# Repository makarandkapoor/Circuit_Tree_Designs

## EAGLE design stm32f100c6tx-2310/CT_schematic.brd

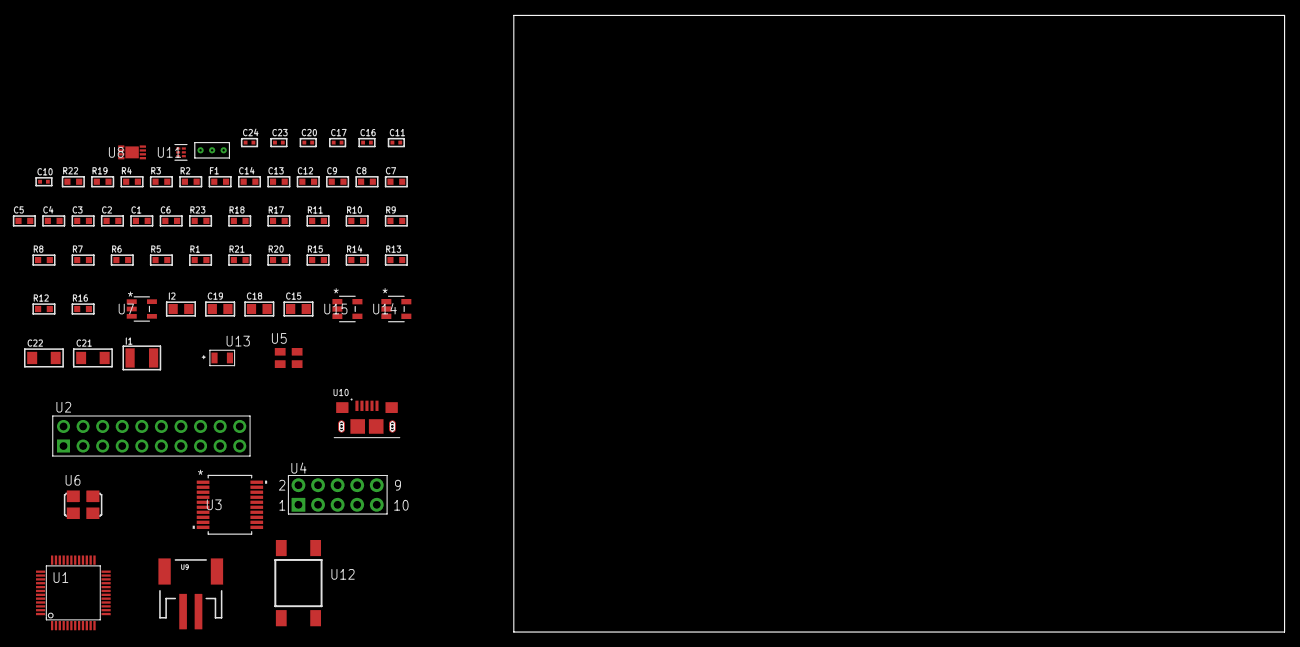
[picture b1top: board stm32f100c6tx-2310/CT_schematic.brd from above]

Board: 2 copper layers, 122.6 x 80.0 mm, 66 parts (0 on the bottom side), 45 nets, no tracks yet.

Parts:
C1, C9, C12, C13, C14: 1e-06; C0603
C2, C3, C4, C5: 1e-07; C0603
C6: 4.7e-06; C0603
C7, C8: 1e-08; C0603
C10, C11, C20: 1e-07; C0402
C15: 4.7e-06; C0805
C16, C17, C23, C24: 1e-08; C0402
C18, C19: 1e-05; C0805
C21, C22: 1e-05; C1206
F1: 240.0; L0603
I1: 1.5e-05; L1210
I2: 2.2e-06; L0805
R1, R5, R6, R7, R8, R9, R10, R11, R17, R18, R23: 10000.0; R0603
R2: 1000.0; R0603
R3: 1600.5; R0603
R4: 4700.0; R0603
R12, R13, R14: 100000.0; R0603
R15: 220000.0; R0603
R16: 1000000.0; R0603
R19: 9100.0; R0603
R20: 680000.0; R0603
R21: 120000.0; R0603
R22: 2000.0; R0603
U1: stm32f100c6t7; LQFP48
U2: TST-110-05-T-D-RA
U3: MAX3218EAP+T; SSOP-20
U4: HTSS-105-01-G-D
U5: ASEK-32.768KHz-ECST; ASEK
U6: ASFL1-25MHZ-NCS; ASFL1
U7: ltc3406es5; TSOT-23-5
U8: MCP73831T-2ACI/MC; DFN8_2X3MC
U9: S2B-PH-SM4-TB(LF)(SN); JST-2-SMD
U10: 10118193-0001LF; FCI_10118193-0001LF
U11: TPS3895ADRYR; SON-6
U12: 4-1437565-2; SW_4-1437565-2
U13: Q65110A2395; LGM67K-G1J2-24-Z
U14, U15: nc7sz125m5x; NC7SZ125M5X
U16: Dummy; DUMMY_PACKAGE_139

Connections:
CLK_U1_3: U1.3, U5.3
CLK_U1_5: U1.5, U6.3
GND: C1.2, C2.2, C3.2, C4.2, C5.2, C6.2, C7.2, C8.2, C9.2, C10.2, C11.2, C12.2, C13.2, C14.2, C16.2, C17.2, C18.2, C19.1, C19.2, C20.2, C21.2, C22.2, C23.2, C24.2, R2.2, R5.2, R11.2, R15.2, R19.2, R21.2, R22.2, U1.8, U1.23, U1.35, U1.47, U2.4, U2.6, U2.8, U2.10, U2.12, U2.14, U2.16, U2.18, U2.20, U3.5, U3.17, U3.20, U4.9, U5.2, U6.2, U7.2, U8.6, U8.9, U9.2, U10.5, U10.6, U10.7, U10.8, U10.9, U11.2, U13.C, U14.2, U14.3, U15.1, U15.3, U16.1
INPUT_USBPOWER_5V: C21.1, R23.2, U8.1, U8.2, U10.1
NET_U1_7: R4.1, U1.7, U15.4
NET_U1_9: C7.1, C8.1, C9.1, F1.1, U1.9
NET_U1_44: R5.1, U1.44
NET_U1_45: R3.1, U1.45, U13.A
NET_U1_46: R1.1, U1.46, U12.3, U12.4
NET_U2_3: R6.1, U2.3
NET_U2_7: R8.1, U2.7
NET_U2_9: R9.1, U2.9
NET_U2_19: R11.1, U2.19
NET_U3_1: I1.1, U3.1
NET_U3_2: R12.1, U3.2
NET_U3_3: R13.1, U3.3
NET_U3_4: R14.1, U3.4
NET_U3_15: C14.1, U3.15
NET_U3_16: C15.2, U3.16
NET_U3_18: C15.1, U3.18
NET_U3_19: C13.1, U3.19
NET_U4_3: U3.12, U4.3
NET_U4_4: U3.11, U4.4
NET_U4_5: U3.14, U4.5
NET_U4_6: U3.13, U4.6
NET_U7_3: I2.1, U7.3
NET_U7_5: R15.1, R16.1, U7.5
NET_U7_ATNET_3: I2.2, R16.2
NET_U8_5: R23.1, U8.5
NET_U8_8: R22.1, U8.8
NET_U11_1: R18.1, R19.1, U11.1
NET_U11_3: R20.2, R21.1, U11.3
NET_U11_4: R17.1, U11.4, U14.4, U15.2
NET_U12_1: R2.1, U12.1, U12.2
PROC_SYS_JTDI: R7.1, U1.38, U2.5
PROC_SYS_JTDO_TRACESWO: U1.39, U2.13
PROC_TIM1_CH1N: U1.17, U16.3
PROC_TIM1_CH3N: U1.19, U16.2
PROC_USART1_CTS: U1.32, U3.8
PROC_USART1_RTS: U1.33, U3.10
PROC_USART1_RX: U1.31, U3.9
PROC_USART1_TX: U1.30, U3.7
RST_OUT_U2_SRESET_B: R10.1, U2.15, U14.1
VCC_S1_3V7: C18.1, C22.1, U7.4, U8.3, U8.4, U9.1
VCC_TIER1_3V3: C1.1, C2.1, C3.1, C4.1, C5.1, C6.1, C10.1, C11.1, C12.1, C16.1, C17.1, C19.2, C20.1, C23.1, C24.1, F1.2, I1.2, I2.2, R1.2, R3.2, R4.2, R6.2, R7.2, R8.2, R9.2, R10.2, R12.2, R13.2, R14.2, R16.2, R17.2, R18.2, R20.1, U1.1, U1.24, U1.36, U1.48, U2.1, U2.2, U3.6, U5.4, U6.4, U11.6, U14.5, U15.5

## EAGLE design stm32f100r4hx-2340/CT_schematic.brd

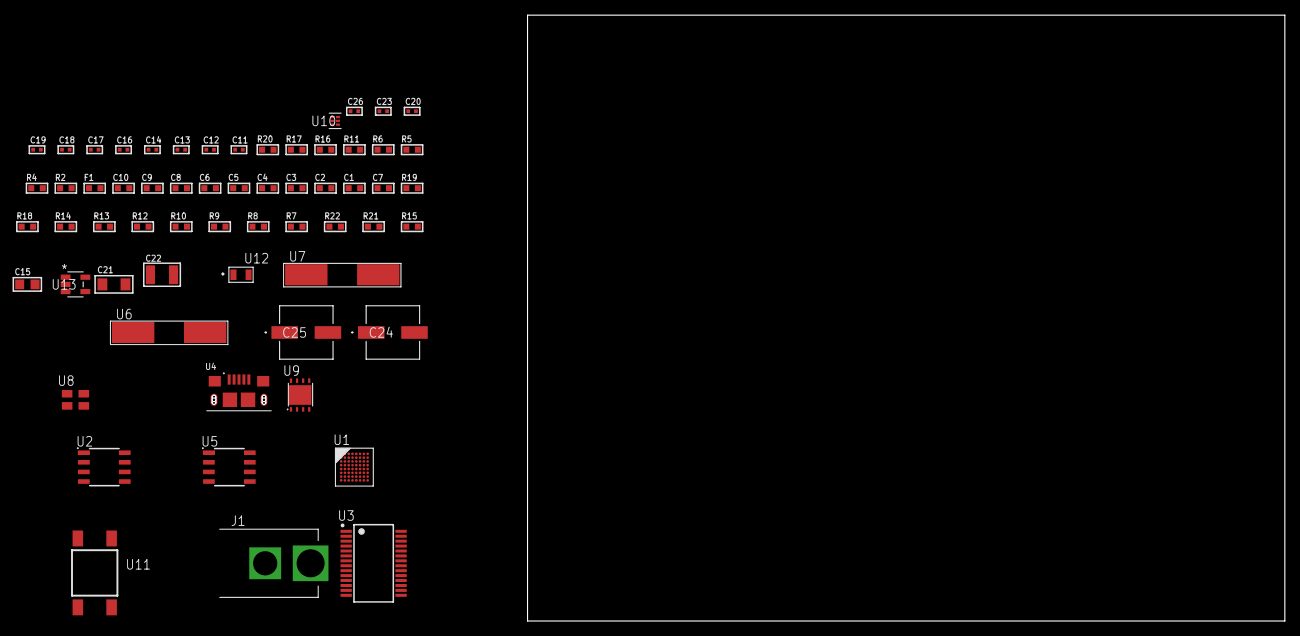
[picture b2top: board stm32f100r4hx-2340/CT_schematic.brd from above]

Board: 2 copper layers, 61 parts (0 on the bottom side), 34 nets, no tracks yet.

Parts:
C1, C10: 1e-06; C0603
C2, C3, C4, C5, C6: 1e-07; C0603
C7: 4.7e-06; C0603
C8, C9: 1e-08; C0603
C11, C12: 1e-11; C0402
C13, C18, C19, C20, C26: 1e-08; C0402
C14, C16, C17, C23: 1e-07; C0402
C15: 4.7e-06; C0805
C21: 1e-05; C1206
C22: 1e-05; C1210
C24, C25: 0.0001; EXV-9H
F1: 240.0; L0603
J1: PJ-037B; PJ-037B_PACKAGE
R2, R17: 1000.0; R0603
R4, R11: 4700.0; R0603
R5, R6: 2200.0; R0603
R7, R8, R9, R10, R12, R13, R14, R18, R19: 10000.0; R0603
R15: 100000.0; R0603
R16: 2231.0; R0603
R20: 9100.0; R0603
R21: 680000.0; R0603
R22: 120000.0; R0603
U1: stm32f100r4h7; TFBGA64
U2: AT25040B-SSHL-T; SOIC-8
U3: FT232RL-REEL; SSOP-28
U4: 10118193-0001LF; FCI_10118193-0001LF
U5: M24M02-DRMN6TP; SOIC-8
U6: ABLS-25.000MHZ-B2F-T
U7: ABLS-12.000MHZ-B4-T
U8: ASEK-32.768KHz-ECST; ASEK
U9: LP3878SDX-ADJ/NOPB; WSON-8
U10: TPS3895ADRYR; SON-6
U11: 4-1437565-2; SW_4-1437565-2
U12: Q65110A2395; LGM67K-G1J2-24-Z
U13: nc7sz125m5x; NC7SZ125M5X

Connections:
CLK_CRYSTAL_U1_C1: C11.1, U1.C1, U6.1
CLK_CRYSTAL_U1_D1: C12.1, U1.D1, U6.2
CLK_CRYSTAL_U3_27: U3.27, U7.1
CLK_CRYSTAL_U3_28: U3.28, U7.2
CLK_U1_A1: U1.A1, U8.3
GND: C1.2, C2.2, C3.2, C4.2, C5.2, C6.2, C7.2, C8.2, C9.2, C10.2, C11.2, C12.2, C13.2, C14.2, C15.2, C16.2, C17.2, C18.2, C19.2, C20.2, C21.2, C22.2, C23.2, C24.2, C25.2, C26.2, J1.2, R2.2, R7.2, R13.2, R14.2, R17.2, R20.2, R22.2, U1.C2, U1.D4, U1.D5, U1.D6, U1.F1, U2.4, U3.7, U3.18, U3.21, U3.25, U3.26, U4.5, U4.6, U4.7, U4.8, U4.9, U5.4, U8.2, U9.3, U9.PAD, U10.2, U12.C, U13.1, U13.3
NET_U1_A3: R6.1, U1.A3, U5.5
NET_U1_B3: R5.1, U1.B3, U5.6
NET_U1_B4: R7.1, U1.B4
NET_U1_E1: R4.1, U1.E1, U13.4
NET_U1_H1: C8.1, C9.1, C10.1, F1.1, U1.G1, U1.H1
NET_U1_H8: U11.3, U11.4
NET_U2_3: R8.1, U2.3
NET_U2_7: R10.1, U2.7
NET_U3_14: R12.1, U3.14
NET_U3_17: C16.1, U3.17
NET_U3_19: R13.1, U3.19
NET_U4_1: R11.1, U4.1
NET_U4_2: U3.16, U4.2
NET_U4_3: U3.15, U4.3
NET_U5_3: R14.1, U5.3
NET_U9_1: C20.1, U9.1
NET_U9_6: R16.2, R17.1, U9.6
NET_U9_8: R15.1, U9.8
NET_U10_1: R19.1, R20.1, U10.1
NET_U10_3: R21.2, R22.1, U10.3
NET_U10_4: R18.1, U10.4, U13.2
NET_U11_1: R2.1, U11.1, U11.2
PROC_SPI1_MISO: U1.A4, U2.2
PROC_SPI1_MOSI: U1.C4, U2.5
PROC_SPI1_NSS: R9.1, U1.A6, U2.1
PROC_SPI1_SCK: U1.A5, U2.6
VCC_S1_5V9: C21.1, C24.1, C25.1, J1.1, R15.2, U9.4
VCC_TIER1_3V3: C1.1, C2.1, C3.1, C4.1, C5.1, C6.1, C7.1, C13.1, C14.1, C15.1, C17.1, C18.1, C19.1, C22.1, C23.1, C26.1, F1.2, R4.2, R5.2, R6.2, R8.2, R9.2, R10.2, R12.2, R16.1, R18.2, R19.2, R21.1, U1.B2, U1.D2, U1.E4, U1.E5, U1.E6, U2.8, U3.4, U3.20, U5.8, U8.4, U9.5, U10.6, U13.5

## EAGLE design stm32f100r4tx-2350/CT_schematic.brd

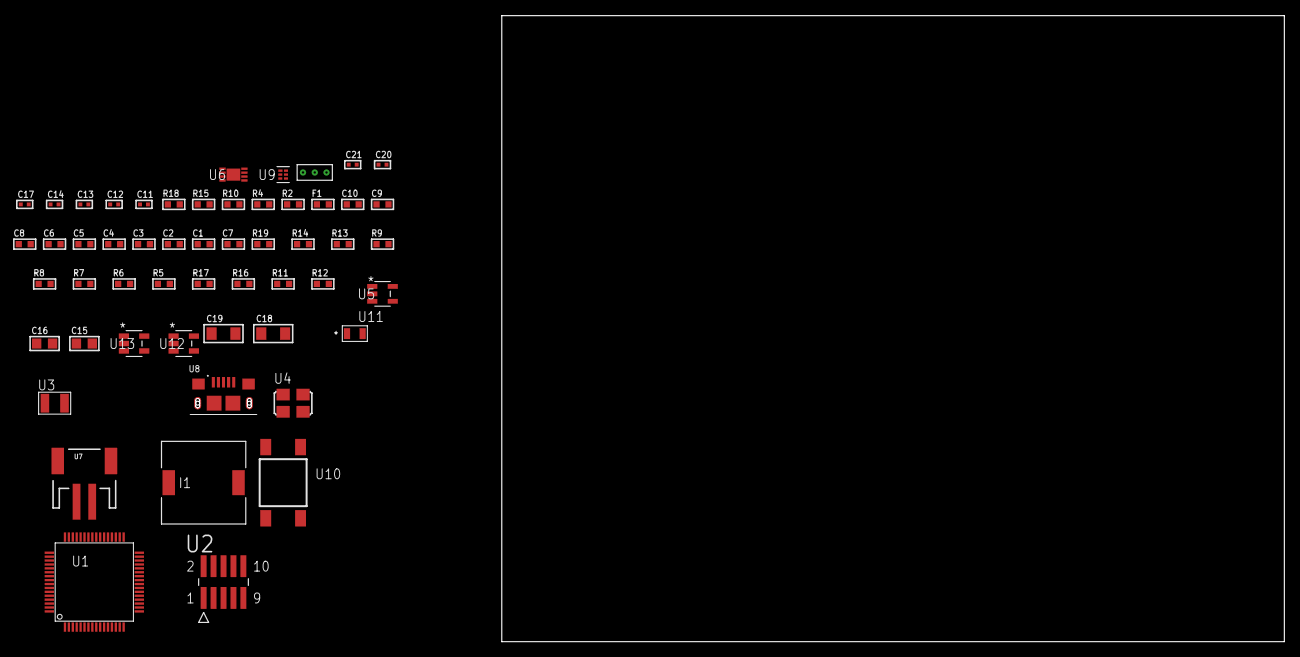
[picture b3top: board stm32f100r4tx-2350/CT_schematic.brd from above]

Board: 2 copper layers, 54 parts (0 on the bottom side), 28 nets, no tracks yet.

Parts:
C1, C10: 1e-06; C0603
C2, C3, C4, C5, C6: 1e-07; C0603
C7: 4.7e-06; C0603
C8, C9: 1e-08; C0603
C11, C12: 1e-11; C0402
C13, C17: 1e-07; C0402
C14, C20, C21: 1e-08; C0402
C15, C16: 1e-05; C0805
C18, C19: 1e-05; C1206
F1: 240.0; L0603
I1: 2.5e-06; DR1040
R2: 1000.0; R0603
R4: 4700.0; R0603
R5, R6, R7, R8, R9, R13, R14, R19: 10000.0; R0603
R10: 5.0; R0603
R11: 220000.0; R0603
R12: 1000000.0; R0603
R15: 9100.0; R0603
R16: 680000.0; R0603
R17: 120000.0; R0603
R18: 2000.0; R0603
U1: stm32f100r4t6; LQFP64
U2: FTSH-105-01-L-DV-K; SAMTEC_FTSH-105-01-L-DV-K
U3: ABS07-32.768KHZ-7-T
U4: ASFL1-25MHZ-NCS; ASFL1
U5: ltc3406es5; TSOT-23-5
U6: MCP73831T-2ACI/MC; DFN8_2X3MC
U7: S2B-PH-SM4-TB(LF)(SN); JST-2-SMD
U8: 10118193-0001LF; FCI_10118193-0001LF
U9: TPS3895ADRYR; SON-6
U10: 4-1437565-2; SW_4-1437565-2
U11: Q65110A2395; LGM67K-G1J2-24-Z
U12, U13: nc7sz125m5x; NC7SZ125M5X
U14: Dummy; DUMMY_PACKAGE_113

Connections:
CLK_CRYSTAL_U1_3: C11.1, U1.3, U3.1
CLK_CRYSTAL_U1_4: C12.1, U1.4, U3.2
CLK_U1_5: U1.5, U4.3
GND: C1.2, C2.2, C3.2, C4.2, C5.2, C6.2, C7.2, C8.2, C9.2, C10.2, C11.2, C12.2, C13.2, C14.2, C15.2, C16.1, C16.2, C17.2, C18.2, C19.2, C20.2, C21.2, R2.2, R5.2, R9.2, R10.2, R11.2, R15.2, R17.2, R18.2, U1.12, U1.18, U1.31, U1.47, U1.63, U2.3, U2.5, U4.2, U5.2, U6.6, U6.9, U7.2, U8.5, U8.6, U8.7, U8.8, U8.9, U9.2, U11.C, U12.2, U12.3, U13.1, U13.3, U14.1
INPUT_USBPOWER_5V: C18.1, R19.2, U6.1, U6.2, U8.1
NET_U1_7: R4.1, U1.7, U13.4
NET_U1_13: C8.1, C9.1, C10.1, F1.1, U1.13
NET_U1_60: R5.1, U1.60
NET_U1_62: U10.3, U10.4
NET_U2_2: R8.1, U2.2
NET_U2_4: R9.1, U2.4
NET_U2_9: R10.1, U2.9
NET_U5_3: I1.1, U5.3
NET_U5_5: R11.1, R12.1, U5.5
NET_U5_ATNET_3: I1.2, R12.2
NET_U6_5: R19.1, U6.5
NET_U6_8: R18.1, U6.8
NET_U9_1: R14.1, R15.1, U9.1
NET_U9_3: R16.2, R17.1, U9.3
NET_U9_4: R13.1, U9.4, U12.4, U13.2
NET_U10_1: R2.1, U10.1, U10.2
PROC_PC13_TAMPER_RTC: U1.2, U14.2
PROC_PD1_OSC_OUT: U1.6, U14.3
PROC_SYS_JTDI: R7.1, U1.50, U2.8
PROC_SYS_JTDO_TRACESWO: U1.55, U2.6
RST_OUT_U2_JTAG_RST_B: R6.1, U2.10, U12.1
VCC_S1_3V7: C15.1, C19.1, U5.4, U6.3, U6.4, U7.1
VCC_TIER1_3V3: C1.1, C2.1, C3.1, C4.1, C5.1, C6.1, C7.1, C13.1, C14.1, C16.2, C17.1, C20.1, C21.1, F1.2, I1.2, R4.2, R6.2, R7.2, R8.2, R12.2, R13.2, R14.2, R16.1, U1.1, U1.19, U1.32, U1.48, U1.64, U2.1, U4.4, U9.6, U12.5, U13.5

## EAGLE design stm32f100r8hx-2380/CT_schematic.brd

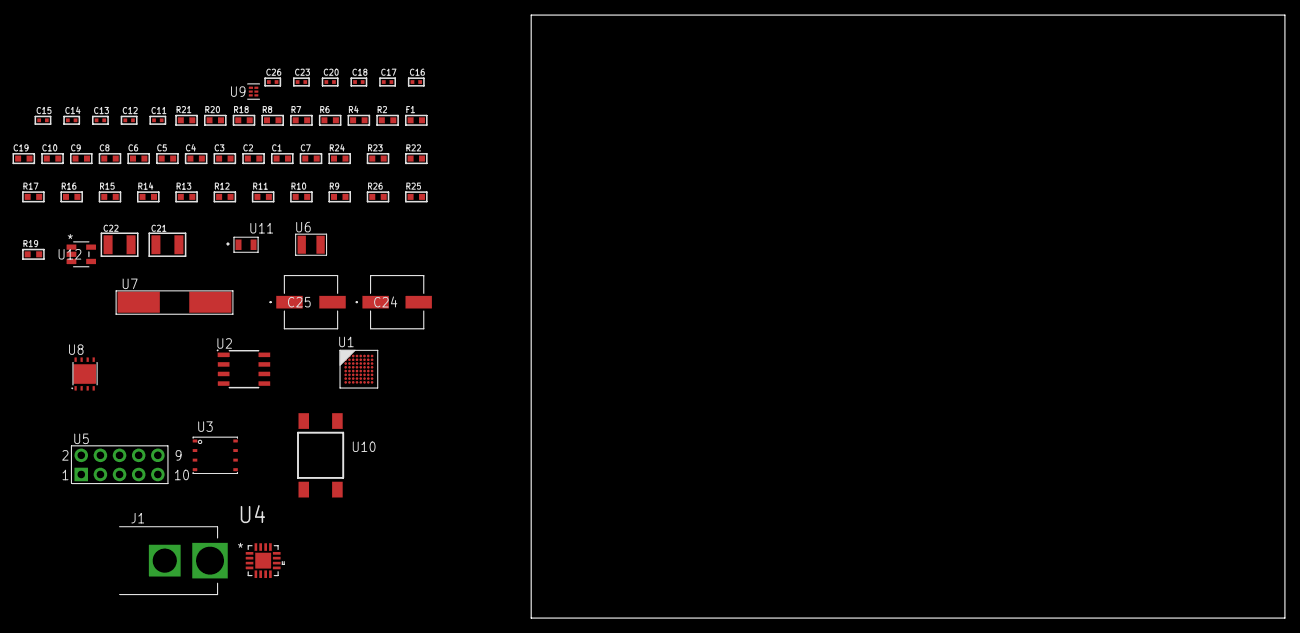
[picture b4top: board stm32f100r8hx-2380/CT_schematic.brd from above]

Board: 2 copper layers, 100.0 x 80.0 mm, 63 parts (0 on the bottom side), 38 nets, no tracks yet.

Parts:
C1, C10, C19: 1e-06; C0603
C2, C3, C4, C5, C6: 1e-07; C0603
C7: 4.7e-06; C0603
C8, C9: 1e-08; C0603
C11, C12, C13, C14: 1e-11; C0402
C15, C16, C20, C26: 1e-08; C0402
C17, C18, C23: 1e-07; C0402
C21, C22: 1e-05; C1210
C24, C25: 0.0001; EXV-9H
F1: 240.0; L0603
J1: PJ-037B; PJ-037B_PACKAGE
R2, R21: 1000.0; R0603
R4: 4700.0; R0603
R6, R7, R8: 2200.0; R0603
R9, R10, R11, R12, R13, R14, R15, R16, R17, R22, R23: 10000.0; R0603
R18: 47.0; R0603
R19: 100000.0; R0603
R20: 1500.0; R0603
R24: 18000.0; R0603
R25: 470000.0; R0603
R26: 120000.0; R0603
U1: stm32f100r8h6; TFBGA64
U2: AT25320B-SSHL-T; SOIC-8
U3: 24AA512-I/MF; DFN8-S
U4: TSC2013QRSARQ1; QFN65P400X400X100-17N
U5: HTSS-105-01-G-D
U6: ABS07-32.768KHZ-7-T
U7: ABLS-25.000MHZ-B2F-T
U8: LP3878SDX-ADJ/NOPB; WSON-8
U9: TPS3895ADRYR; SON-6
U10: 4-1437565-2; SW_4-1437565-2
U11: Q65110A2395; LGM67K-G1J2-24-Z
U12: nc7sz125m5x; NC7SZ125M5X

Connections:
CLK_CRYSTAL_U1_A1: C11.1, U1.A1, U6.1
CLK_CRYSTAL_U1_B1: C12.1, U1.B1, U6.2
CLK_CRYSTAL_U1_C1: C13.1, U1.C1, U7.1
CLK_CRYSTAL_U1_D1: C14.1, U1.D1, U7.2
GND: C1.2, C2.2, C3.2, C4.2, C5.2, C6.2, C7.2, C8.2, C9.2, C10.2, C11.2, C12.2, C13.2, C14.2, C15.2, C16.2, C20.2, C21.2, C22.2, C23.2, C24.2, C25.2, C26.2, J1.2, R2.2, R9.2, R13.2, R21.2, R24.2, R26.2, U1.C2, U1.D4, U1.D5, U1.D6, U1.F1, U2.4, U3.4, U4.17, U5.9, U8.3, U8.PAD, U9.2, U11.C, U12.1, U12.3
NET_U1_A3: R6.1, U1.A3, U4.1
NET_U1_B4: R9.1, U1.B4
NET_U1_E1: R4.1, U1.E1, U12.4
NET_U1_G7: R7.1, U1.G7, U3.6
NET_U1_H1: C8.1, C9.1, C10.1, F1.1, U1.G1, U1.H1
NET_U1_H7: R8.1, U1.H7, U3.5
NET_U1_H8: U10.3, U10.4
NET_U2_3: R10.1, U2.3
NET_U2_7: R12.1, U2.7
NET_U3_1: R13.1, U3.1
NET_U3_2: R14.1, U3.2
NET_U3_3: R15.1, U3.3
NET_U4_4: R17.1, U4.4
NET_U4_5: R16.1, U4.5
NET_U4_9: C17.2, C18.2, C19.2, R18.2, U4.9
NET_U4_15: R18.1, U4.8, U4.15
NET_U5_3: U4.12, U5.3
NET_U5_4: U4.14, U5.4
NET_U5_5: U4.11, U5.5
NET_U5_6: U4.13, U5.6
NET_U8_1: C20.1, U8.1
NET_U8_6: R20.2, R21.1, U8.6
NET_U8_8: R19.1, U8.8
NET_U9_1: R23.1, R24.1, U9.1
NET_U9_3: R25.2, R26.1, U9.3
NET_U9_4: R22.1, U9.4, U12.2
NET_U10_1: R2.1, U10.1, U10.2
PROC_SPI1_MISO: U1.A4, U2.2
PROC_SPI1_MOSI: U1.C4, U2.5
PROC_SPI1_NSS: R11.1, U1.A6, U2.1
PROC_SPI1_SCK: U1.A5, U2.6
VCC_S1_11V6: C21.1, C24.1, C25.1, J1.1, R19.2, U8.4
VCC_TIER1_2V5: C1.1, C2.1, C3.1, C4.1, C5.1, C6.1, C7.1, C15.1, C16.1, C17.1, C18.1, C19.1, C22.1, C23.1, C26.1, F1.2, R4.2, R6.2, R7.2, R8.2, R10.2, R11.2, R12.2, R14.2, R15.2, R16.2, R17.2, R20.1, R22.2, R23.2, R25.1, U1.B2, U1.D2, U1.E4, U1.E5, U1.E6, U2.8, U3.7, U3.8, U4.7, U4.10, U8.5, U9.6, U12.5

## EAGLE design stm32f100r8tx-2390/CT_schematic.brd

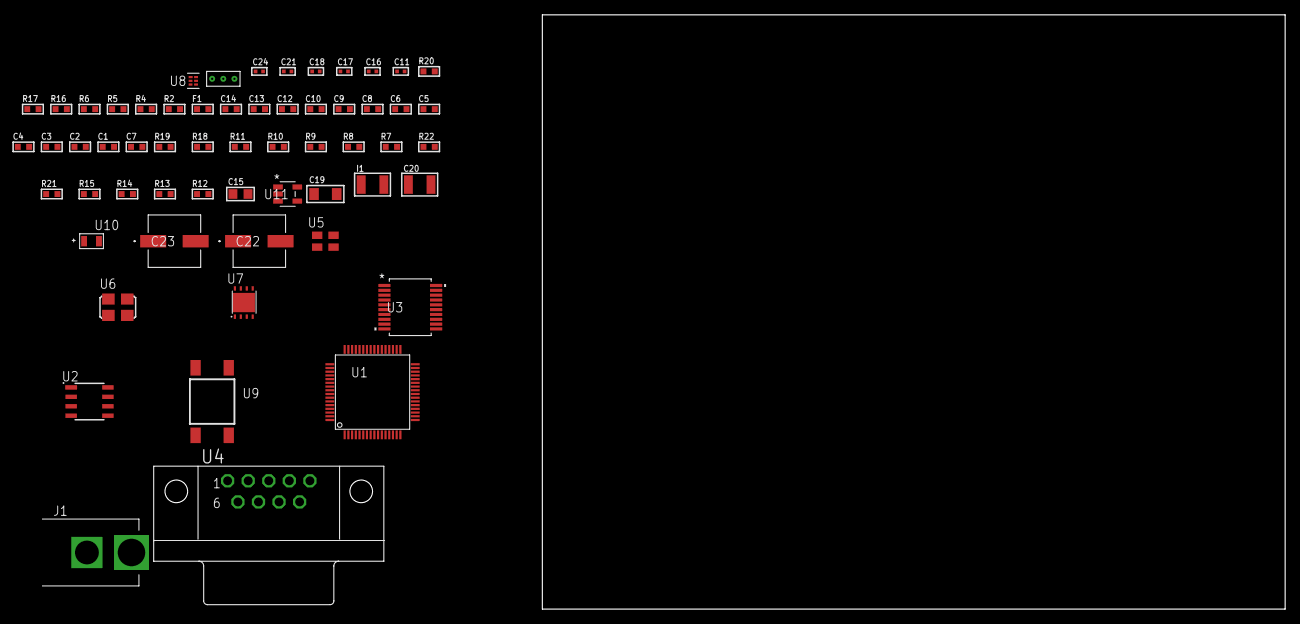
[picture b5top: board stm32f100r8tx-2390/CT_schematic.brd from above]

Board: 2 copper layers, 100.0 x 80.0 mm, 59 parts (0 on the bottom side), 40 nets, no tracks yet.

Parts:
C1, C10, C12, C13, C14: 1e-06; C0603
C2, C3, C4, C5, C6: 1e-07; C0603
C7: 4.7e-06; C0603
C8, C9: 1e-08; C0603
C11, C16, C17, C18, C24: 1e-08; C0402
C15: 4.7e-06; C0805
C19: 1e-05; C1206
C20: 1e-05; C1210
C21: 1e-07; C0402
C22, C23: 0.0001; EXV-9H
F1: 240.0; L0603
I1: 1.5e-05; L1210
J1: PJ-037B; PJ-037B_PACKAGE
R2, R17: 1000.0; R0603
R4: 4700.0; R0603
R5, R6: 2200.0; R0603
R7, R8, R9, R10, R11, R18, R19: 10000.0; R0603
R12, R13, R14, R15: 100000.0; R0603
R16: 2231.0; R0603
R20: 9100.0; R0603
R21: 680000.0; R0603
R22: 120000.0; R0603
U1: stm32f100r8t6; LQFP64
U2: AT24C02D-SSHM-T; AT24C02D
U3: MAX3218EAP+T; SSOP-20
U4: 182-009-113R531; 182-009-MALE
U5: ASEK-32.768KHz-ECST; ASEK
U6: ASFL1-25MHZ-NCS; ASFL1
U7: LP3878SDX-ADJ/NOPB; WSON-8
U8: TPS3895ADRYR; SON-6
U9: 4-1437565-2; SW_4-1437565-2
U10: Q65110A2395; LGM67K-G1J2-24-Z
U11: nc7sz125m5x; NC7SZ125M5X
U12: Dummy; DUMMY_PACKAGE_124

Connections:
CLK_U1_3: U1.3, U5.3
CLK_U1_5: U1.5, U6.3
GND: C1.2, C2.2, C3.2, C4.2, C5.2, C6.2, C7.2, C8.2, C9.2, C10.2, C11.2, C12.2, C13.2, C14.2, C16.2, C17.2, C18.2, C19.2, C20.2, C21.2, C22.2, C23.2, C24.2, J1.2, R2.2, R7.2, R8.2, R10.2, R11.2, R17.2, R20.2, R22.2, U1.12, U1.18, U1.31, U1.47, U1.63, U2.4, U3.5, U3.17, U3.20, U4.5, U5.2, U6.2, U7.3, U7.PAD, U8.2, U10.C, U11.1, U11.3, U12.1
NET_U1_7: R4.1, U1.7, U11.4
NET_U1_13: C8.1, C9.1, C10.1, F1.1, U1.13
NET_U1_58: R5.1, U1.58, U2.6
NET_U1_59: R6.1, U1.59, U2.5
NET_U1_60: R7.1, U1.60
NET_U1_62: U9.3, U9.4
NET_U2_1: R9.1, U2.1
NET_U2_2: R10.1, U2.2
NET_U2_3: R11.1, U2.3
NET_U2_7: R8.1, U2.7
NET_U3_1: I1.1, U3.1
NET_U3_2: R12.1, U3.2
NET_U3_3: R13.1, U3.3
NET_U3_4: R14.1, U3.4
NET_U3_15: C14.1, U3.15
NET_U3_16: C15.2, U3.16
NET_U3_18: C15.1, U3.18
NET_U3_19: C13.1, U3.19
NET_U4_2: U3.12, U4.2
NET_U4_3: U3.14, U4.3
NET_U4_7: U3.11, U4.7
NET_U4_8: U3.13, U4.8
NET_U7_1: C18.1, U7.1
NET_U7_6: R16.2, R17.1, U7.6
NET_U7_8: R15.1, U7.8
NET_U8_1: R19.1, R20.1, U8.1
NET_U8_3: R21.2, R22.1, U8.3
NET_U8_4: R18.1, U8.4, U11.2
NET_U9_1: R2.1, U9.1, U9.2
PROC_ADC1_IN3: U1.17, U12.3
PROC_ADC1_IN4: U1.20, U12.2
PROC_USART1_CTS: U1.44, U3.8
PROC_USART1_RTS: U1.45, U3.10
PROC_USART1_RX: U1.43, U3.9
PROC_USART1_TX: U1.42, U3.7
VCC_S1_10V1: C19.1, C22.1, C23.1, J1.1, R15.2, U7.4
VCC_TIER1_3V3: C1.1, C2.1, C3.1, C4.1, C5.1, C6.1, C7.1, C11.1, C12.1, C16.1, C17.1, C20.1, C21.1, C24.1, F1.2, I1.2, R4.2, R5.2, R6.2, R9.2, R12.2, R13.2, R14.2, R16.1, R18.2, R19.2, R21.1, U1.1, U1.19, U1.32, U1.48, U1.64, U2.8, U3.6, U5.4, U6.4, U7.5, U8.6, U11.5

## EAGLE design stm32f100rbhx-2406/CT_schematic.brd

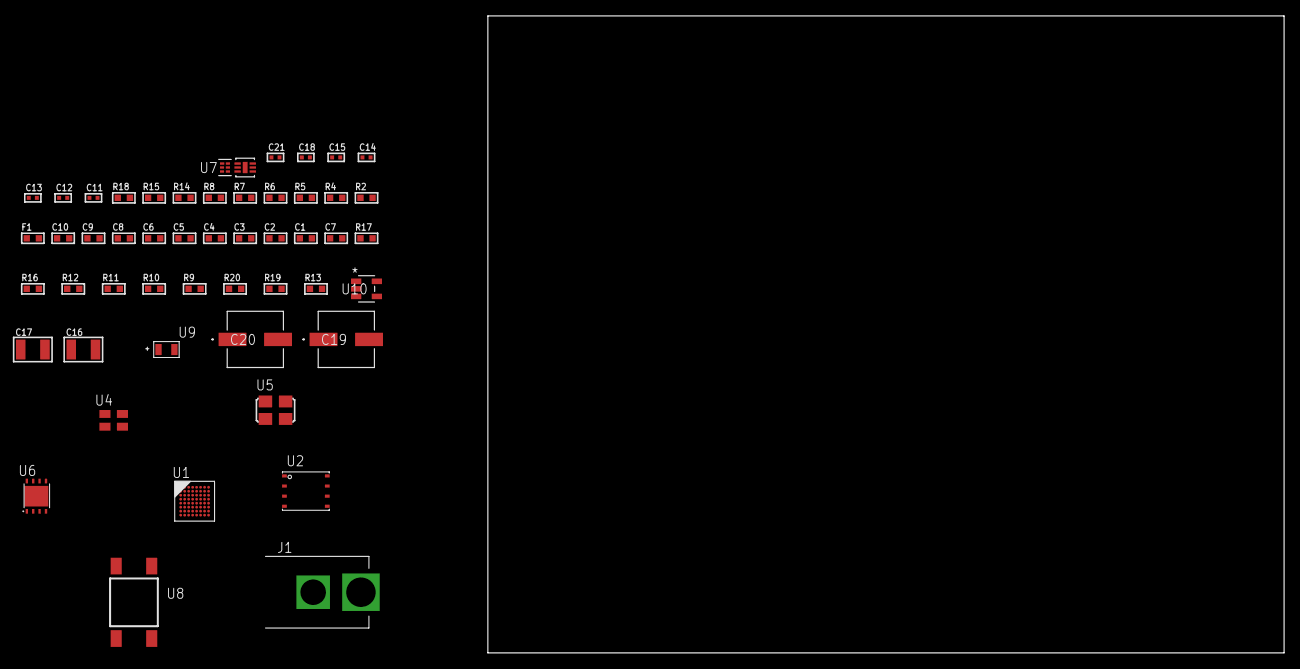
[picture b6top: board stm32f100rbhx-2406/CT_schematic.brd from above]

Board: 2 copper layers, 100.0 x 80.0 mm, 51 parts (0 on the bottom side), 23 nets, no tracks yet.

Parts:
C1, C10: 1e-06; C0603
C2, C3, C4, C5, C6: 1e-07; C0603
C7: 4.7e-06; C0603
C8, C9: 1e-08; C0603
C11, C13, C14, C15, C21: 1e-08; C0402
C12, C18: 1e-07; C0402
C16, C17: 1e-05; C1210
C19, C20: 0.0001; EXV-9H
F1: 240.0; L0603
J1: PJ-037B; PJ-037B_PACKAGE
R2, R15: 1000.0; R0603
R4: 4700.0; R0603
R5, R6, R7, R8: 2200.0; R0603
R9, R10, R11, R12, R16, R17: 10000.0; R0603
R13: 100000.0; R0603
R14: 2231.0; R0603
R18: 9100.0; R0603
R19: 680000.0; R0603
R20: 120000.0; R0603
U1: stm32f100rbh7; TFBGA64
U2: 24AA512-I/MF; DFN8-S
U3: SI7006-A20-IM; DFN-6
U4: ASEK-32.768KHz-ECST; ASEK
U5: ASFL1-25MHZ-NCS; ASFL1
U6: LP3878SDX-ADJ/NOPB; WSON-8
U7: TPS3895ADRYR; SON-6
U8: 4-1437565-2; SW_4-1437565-2
U9: Q65110A2395; LGM67K-G1J2-24-Z
U10: nc7sz125m5x; NC7SZ125M5X

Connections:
CLK_U1_A1: U1.A1, U4.3
CLK_U1_C1: U1.C1, U5.3
GND: C1.2, C2.2, C3.2, C4.2, C5.2, C6.2, C7.2, C8.2, C9.2, C10.2, C11.2, C12.2, C13.2, C14.2, C15.2, C16.2, C17.2, C18.2, C19.2, C20.2, C21.2, J1.2, R2.2, R9.2, R11.2, R12.2, R15.2, R18.2, R20.2, U1.C2, U1.D4, U1.D5, U1.D6, U1.F1, U2.4, U2.7, U3.2, U3.7, U4.2, U5.2, U6.3, U6.PAD, U7.2, U9.C, U10.1, U10.3
NET_U1_A3: R6.1, U1.A3, U3.1
NET_U1_B3: R5.1, U1.B3, U3.6
NET_U1_B4: R9.1, U1.B4
NET_U1_E1: R4.1, U1.E1, U10.4
NET_U1_G7: R7.1, U1.G7, U2.6
NET_U1_H1: C8.1, C9.1, C10.1, F1.1, U1.G1, U1.H1
NET_U1_H7: R8.1, U1.H7, U2.5
NET_U1_H8: U8.3, U8.4
NET_U2_1: R10.1, U2.1
NET_U2_2: R11.1, U2.2
NET_U2_3: R12.1, U2.3
NET_U6_1: C15.1, U6.1
NET_U6_6: R14.2, R15.1, U6.6
NET_U6_8: R13.1, U6.8
NET_U7_1: R17.1, R18.1, U7.1
NET_U7_3: R19.2, R20.1, U7.3
NET_U7_4: R16.1, U7.4, U10.2
NET_U8_1: R2.1, U8.1, U8.2
VCC_S1_15V8: C16.1, C19.1, C20.1, J1.1, R13.2, U6.4
VCC_TIER1_3V3: C1.1, C2.1, C3.1, C4.1, C5.1, C6.1, C7.1, C11.1, C12.1, C13.1, C14.1, C17.1, C18.1, C21.1, F1.2, R4.2, R5.2, R6.2, R7.2, R8.2, R10.2, R14.1, R16.2, R17.2, R19.1, U1.B2, U1.D2, U1.E4, U1.E5, U1.E6, U2.8, U3.5, U4.4, U5.4, U6.5, U7.6, U10.5

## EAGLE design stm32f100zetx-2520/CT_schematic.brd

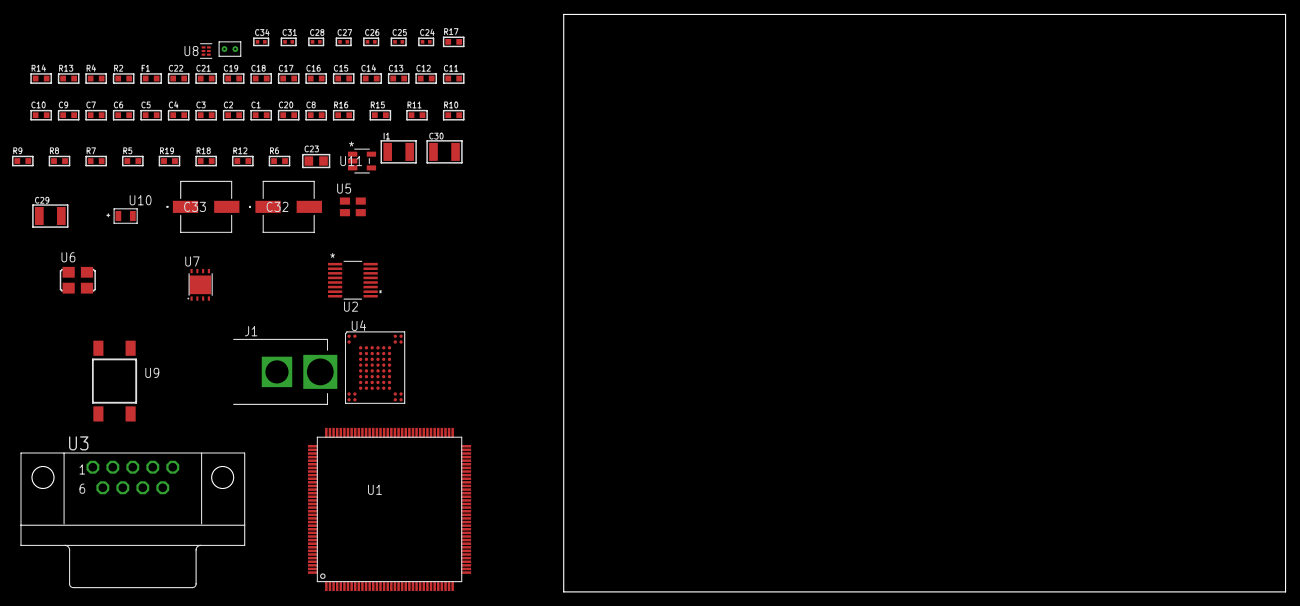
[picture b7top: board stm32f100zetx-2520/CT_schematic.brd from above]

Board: 2 copper layers, 100.0 x 80.0 mm, 66 parts (0 on the bottom side), 41 nets, no tracks yet.

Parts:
C1, C17, C18, C19, C21, C22: 1e-06; C0603
C2, C3, C4, C5, C6, C7, C9, C10, C11, C12, C13, C14: 1e-07; C0603
C8: 4.7e-06; C0603
C15, C16: 1e-08; C0603
C20: 2.2e-07; C0603
C23: 1e-05; C0805
C24, C25, C31: 1e-07; C0402
C26, C27, C28, C34: 1e-08; C0402
C29, C30: 1e-05; C1210
C32, C33: 0.0001; EXV-9H
F1: 240.0; L0603
I1: 1e-05; L1210
J1: PJ-037B; PJ-037B_PACKAGE
R2, R14: 1000.0; R0603
R4: 4700.0; R0603
R5, R7, R8, R9, R10, R11, R15, R16: 10000.0; R0603
R6, R12: 100000.0; R0603
R13: 2231.0; R0603
R17: 9100.0; R0603
R18: 680000.0; R0603
R19: 120000.0; R0603
U1: stm32f100zet6; LQFP144
U2: LTC2804CGN-1#PBF; SSOP-16
U3: 182-009-113R531; 182-009-MALE
U4: TH58NVG3S0HBAI4
U5: ASEK-32.768KHz-ECST; ASEK
U6: ASFL1-25MHZ-NCS; ASFL1
U7: LP3878SDX-ADJ/NOPB; WSON-8
U8: TPS3895ADRYR; SON-6
U9: 4-1437565-2; SW_4-1437565-2
U10: Q65110A2395; LGM67K-G1J2-24-Z
U11: nc7sz125m5x; NC7SZ125M5X
U12: Dummy; DUMMY_PACKAGE_140

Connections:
CLK_U1_8: U1.8, U5.3
CLK_U1_23: U1.23, U6.3
GND: C1.2, C2.2, C3.2, C4.2, C5.2, C6.2, C7.2, C8.2, C9.2, C10.2, C11.2, C12.2, C13.2, C14.2, C15.2, C16.2, C17.2, C18.2, C19.2, C21.2, C22.2, C23.2, C24.2, C25.2, C26.2, C27.2, C28.2, C29.2, C30.2, C31.2, C32.2, C33.2, C34.2, J1.2, R2.2, R5.2, R14.2, R17.2, R19.2, U1.16, U1.30, U1.31, U1.38, U1.51, U1.61, U1.71, U1.83, U1.94, U1.107, U1.120, U1.130, U1.143, U2.8, U3.5, U4.C5, U4.K3, U4.K8, U5.2, U6.2, U7.3, U7.PAD, U8.2, U10.C, U11.1, U11.3, U12.1
NET_U1_25: R4.1, U1.25, U11.4
NET_U1_33: C15.1, C16.1, C17.1, F1.1, U1.32, U1.33
NET_U1_138: R5.1, U1.138
NET_U1_142: U9.3, U9.4
NET_U2_6: C18.1, U2.6
NET_U2_7: C20.1, I1.2, U2.7
NET_U2_9: C19.1, U2.9
NET_U2_10: C20.2, U2.10
NET_U2_11: R6.1, U2.11
NET_U3_2: U2.1, U3.2
NET_U3_3: U2.3, U3.3
NET_U3_7: U2.2, U3.7
NET_U3_8: U2.4, U3.8
NET_U4_C3: R10.1, U4.C3
NET_U4_C6: R7.1, U4.C6
NET_U4_C8: R11.1, U4.C8
NET_U7_1: C28.1, U7.1
NET_U7_6: R13.2, R14.1, U7.6
NET_U7_8: R12.1, U7.8
NET_U8_1: R16.1, R17.1, U8.1
NET_U8_3: R18.2, R19.1, U8.3
NET_U8_4: R15.1, U8.4, U11.2
NET_U9_1: R2.1, U9.1, U9.2
PROC_DAC_OUT2: U1.41, U12.2
PROC_FSMC_D0: U1.85, U4.H4
PROC_FSMC_D1: U1.86, U4.J4
PROC_FSMC_D2: U1.114, U4.K4
PROC_FSMC_D3: U1.115, U4.K5
PROC_FSMC_D4: U1.58, U4.K6
PROC_FSMC_D5: U1.59, U4.J7
PROC_FSMC_D6: U1.60, U4.K7
PROC_FSMC_D7: U1.63, U4.J8
PROC_FSMC_NOE: R8.1, U1.118, U4.D4
PROC_FSMC_NWE: R9.1, U1.119, U4.C7
PROC_UART4_RX: U1.112, U2.16
PROC_UART4_TX: U1.111, U2.14
VCC_S1_12V7: C29.1, C32.1, C33.1, J1.1, R12.2, U7.4
VCC_TIER1_3V3: C1.1, C2.1, C3.1, C4.1, C5.1, C6.1, C7.1, C8.1, C9.1, C10.1, C11.1, C12.1, C13.1, C14.1, C21.1, C22.1, C23.1, C24.1, C25.1, C26.1, C27.1, C30.1, C31.1, C34.1, F1.2, I1.1, R4.2, R6.2, R7.2, R8.2, R9.2, R10.2, R11.2, R13.1, R15.2, R16.2, R18.1, U1.6, U1.17, U1.39, U1.52, U1.62, U1.72, U1.84, U1.95, U1.108, U1.121, U1.131, U1.144, U2.5, U2.12, U4.H8, U4.J6, U5.4, U6.4, U7.5, U8.6, U11.5

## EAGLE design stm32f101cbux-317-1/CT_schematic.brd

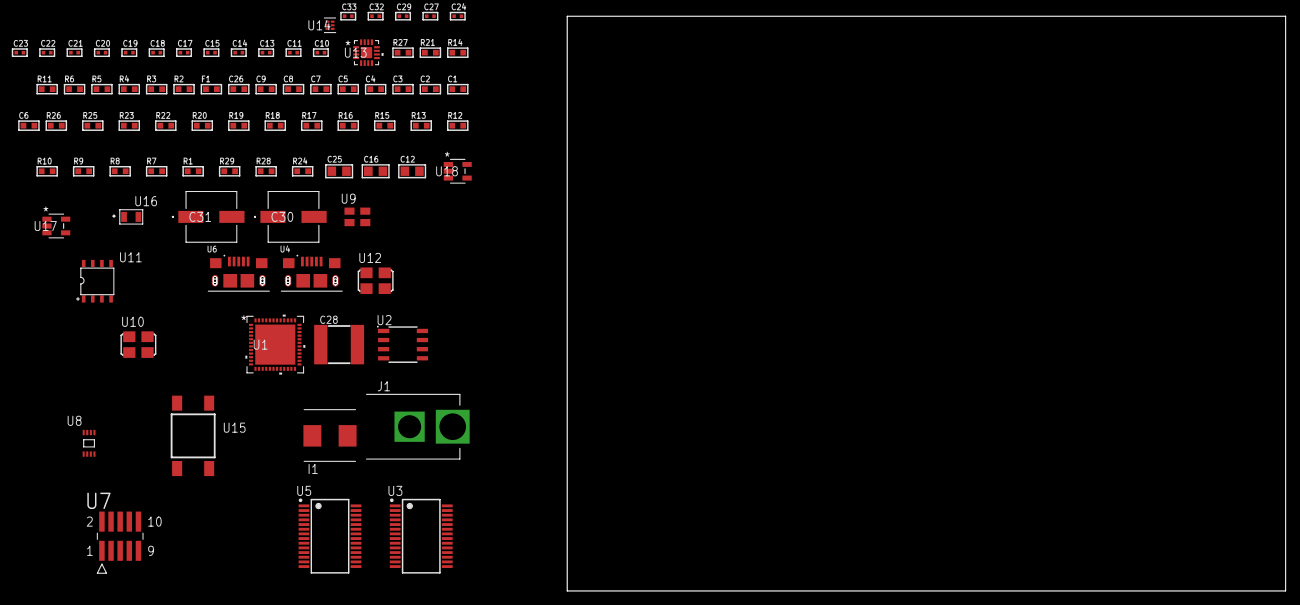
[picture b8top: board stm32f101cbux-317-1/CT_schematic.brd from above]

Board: 2 copper layers, 83 parts (0 on the bottom side), 56 nets, no tracks yet.

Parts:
C1, C9, C26: 1e-06; C0603
C2, C3, C4, C5: 1e-07; C0603
C6: 4.7e-06; C0603
C7, C8: 1e-08; C0603
C10, C20, C21, C22, C23, C24, C32, C33: 1e-08; C0402
C11, C13, C14, C15, C17, C18, C19, C27, C29: 1e-07; C0402
C12, C16: 4.7e-06; C0805
C25: 1e-05; C0805
C28: 6.8e-05; 2220
C30, C31: 0.0001; EXV-9H
F1: 240.0; L0603
I1: 3.3e-06; WE-HCI_7030/7040/7050
J1: PJ-037B; PJ-037B_PACKAGE
R1, R7, R8, R9, R10, R12, R13, R15, R16, R17, R18, R19, R20, R25, R26: 10000.0; R0603
R2: 1000.0; R0603
R3: 1600.5; R0603
R4, R11, R14: 4700.0; R0603
R5, R6: 2200.0; R0603
R21: 5.0; R0603
R22: 20000.0; R0603
R23: 91000.0; R0603
R24: 300000.0; R0603
R27: 9100.0; R0603
R28: 680000.0; R0603
R29: 120000.0; R0603
U1: STM32F101CBU6; UFQFPN48
U2: AT25512N-SH-T; SOIC-8
U3, U5: FT232RL-REEL; SSOP-28
U4, U6: 10118193-0001LF; FCI_10118193-0001LF
U7: FTSH-105-01-L-DV-K; SAMTEC_FTSH-105-01-L-DV-K
U8: 24AA02T-I/MNY; TDFN-8/6MM
U9: ASEK-32.768KHz-ECST; ASEK
U10: ASFL1-12MHZ-NCS; ASFL1
U11: idt74fct38072; IDT74FCT38072
U12: ASFL1-25MHZ-NCS; ASFL1
U13: LTC3601EUD#PBF; QFN-16_EP
U14: TPS3895ADRYR; SON-6
U15: 4-1437565-2; SW_4-1437565-2
U16: Q65110A2395; LGM67K-G1J2-24-Z
U17, U18: nc7sz125m5x; NC7SZ125M5X

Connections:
CLK_U1_3: U1.3, U9.3
CLK_U1_5: U1.5, U12.3
CLK_U3_27: U3.27, U11.7
CLK_U5_27: U5.27, U11.6
CLK_U11_3: U10.3, U11.3
GND: C1.2, C2.2, C3.2, C4.2, C5.2, C6.2, C7.2, C8.2, C9.2, C10.2, C11.2, C12.2, C13.2, C14.2, C15.2, C16.2, C17.2, C18.2, C19.2, C20.2, C21.2, C22.2, C23.2, C24.2, C25.2, C26.2, C28.1, C28.2, C29.2, C30.2, C31.2, C32.2, C33.2, J1.2, R2.2, R7.2, R13.2, R16.2, R20.2, R21.2, R22.2, R24.2, R27.2, R29.2, U1.8, U1.23, U1.35, U1.47, U1.49, U2.4, U3.7, U3.18, U3.21, U3.25, U3.26, U4.5, U4.6, U4.7, U4.8, U4.9, U5.7, U5.18, U5.21, U5.25, U5.26, U6.5, U6.6, U6.7, U6.8, U6.9, U7.3, U7.5, U8.4, U8.7, U9.2, U10.2, U11.4, U11.5, U11.8, U12.2, U13.1, U13.9, U13.17, U14.2, U16.C, U17.2, U17.3, U18.1, U18.3
NET_U1_7: R4.1, U1.7, U18.4
NET_U1_9: C7.1, C8.1, C9.1, F1.1, U1.9
NET_U1_42: R5.1, U1.42, U8.6
NET_U1_43: R6.1, U1.43, U8.5
NET_U1_44: R7.1, U1.44
NET_U1_45: R3.1, U1.45, U16.A
NET_U1_46: R1.1, U1.46, U15.3, U15.4
NET_U2_3: R8.1, U2.3
NET_U2_7: R10.1, U2.7
NET_U3_14: R12.1, U3.14
NET_U3_17: C13.1, U3.17
NET_U3_19: R13.1, U3.19
NET_U4_1: R11.1, U4.1
NET_U4_2: U3.16, U4.2
NET_U4_3: U3.15, U4.3
NET_U5_14: R15.1, U5.14
NET_U5_17: C17.1, U5.17
NET_U5_19: R16.1, U5.19
NET_U6_1: R14.1, U6.1
NET_U6_2: U5.16, U6.2
NET_U6_3: U5.15, U6.3
NET_U7_2: R19.1, U7.2
NET_U7_4: R20.1, U7.4
NET_U7_9: R21.1, U7.9
NET_U13_3: C27.2, I1.1, U13.3, U13.4
NET_U13_6: C27.1, U13.6
NET_U13_7: C26.1, U13.7, U13.12
NET_U13_10: R24.1, U13.10
NET_U13_11: R22.1, R23.1, U13.11
NET_U13_ATNET_3: I1.2, R23.2
NET_U14_1: R26.1, R27.1, U14.1
NET_U14_3: R28.2, R29.1, U14.3
NET_U14_4: R25.1, U14.4, U17.4, U18.2
NET_U15_1: R2.1, U15.1, U15.2
PROC_SPI1_MISO: U1.16, U2.2
PROC_SPI1_MOSI: U1.17, U2.5
PROC_SPI1_NSS: R9.1, U1.14, U2.1
PROC_SPI1_SCK: U1.15, U2.6
PROC_SYS_JTDI: R18.1, U1.38, U7.8
PROC_SYS_JTDO_TRACESWO: U1.39, U7.6
PROC_USART1_CTS: U1.32, U3.3
PROC_USART1_RX: U1.31, U3.1
PROC_USART1_TX: U1.30, U3.5
PROC_USART2_CTS: U1.10, U5.3
PROC_USART2_RTS: U1.11, U5.11
PROC_USART2_RX: U1.13, U5.1
PROC_USART2_TX: U1.12, U5.5
RST_OUT_U7_JTAG_RST_B: R17.1, U7.10, U17.1
VCC_S1_6V5: C25.1, C30.1, C31.1, J1.1, U13.15, U13.16
VCC_TIER1_3V3: C1.1, C2.1, C3.1, C4.1, C5.1, C6.1, C10.1, C11.1, C12.1, C14.1, C15.1, C16.1, C18.1, C19.1, C20.1, C21.1, C22.1, C23.1, C24.1, C28.2, C29.1, C32.1, C33.1, F1.2, I1.2, R1.2, R3.2, R4.2, R5.2, R6.2, R8.2, R9.2, R10.2, R12.2, R15.2, R17.2, R18.2, R19.2, R23.2, R25.2, R26.2, R28.1, U1.1, U1.24, U1.36, U1.48, U2.8, U3.4, U3.20, U5.4, U5.20, U7.1, U8.8, U9.4, U10.4, U11.1, U11.2, U12.4, U13.8, U14.6, U17.5, U18.5
